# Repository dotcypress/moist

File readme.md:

# moist

🌻 Soil Moisture Sensor

# Resources

* [Schematics](https://kicanvas.org/?github=https://github.com/dotcypress/moist/blob/main/pcb/moist.kicad_sch)
* [PCB](https://kicanvas.org/?github=https%3A%2F%2Fgithub.com%2Fdotcypress%2Fmoist%2Fblob%2Fmain%2Fpcb%2Fmoist.kicad_pcb)
* [BOM](https://htmlpreview.github.io/?https://github.com/dotcypress/moist/blob/main/pcb/bom/ibom.html)

## License

Licensed under either of

- Apache License, Version 2.0 ([LICENSE-APACHE](LICENSE-APACHE) or
  http://www.apache.org/licenses/LICENSE-2.0)
- MIT license ([LICENSE-MIT](LICENSE-MIT) or http://opensource.org/licenses/MIT)

at your option.

### Contribution

Unless you explicitly state otherwise, any contribution intentionally submitted
for inclusion in the work by you, as defined in the Apache-2.0 license, shall be
dual licensed as above, without any additional terms or conditions.

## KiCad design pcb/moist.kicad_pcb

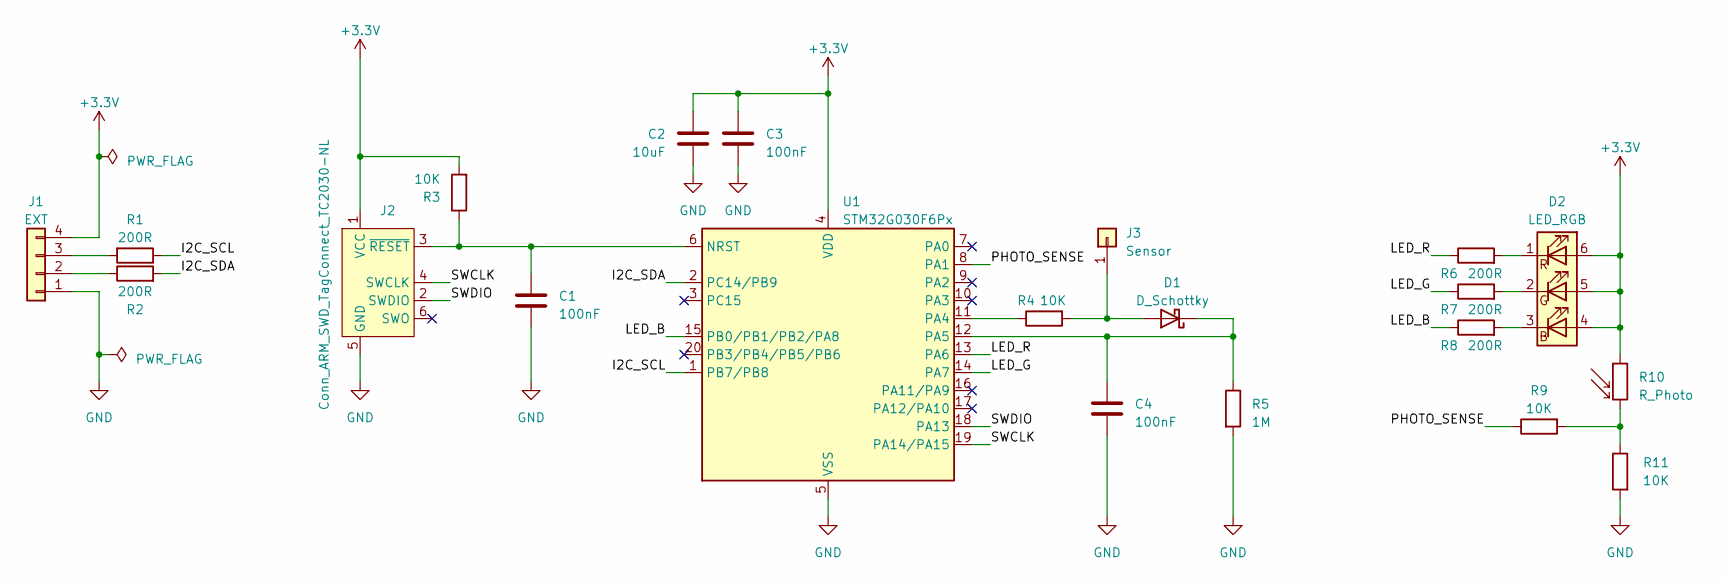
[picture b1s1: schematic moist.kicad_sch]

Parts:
C1, C3, C4: 100nF; C_0603_1608Metric
C2: 10uF; C_0603_1608Metric
D1: D_Schottky; D_0603_1608Metric
D2: LED_RGB; LED_RGB_PLCC-6
J1: EXT; SolderWire-0.1sqmm_1x04_P3.6mm_D0.4mm_OD1mm_Relief
J2: Conn_ARM_SWD_TagConnect_TC2030-NL; Tag-Connect_TC2030-IDC-NL_2x03_P1.27mm_Vertical
J3: Sensor; SensorPad
R1, R2, R6, R7, R8: 200R; R_0603_1608Metric
R3, R4, R9, R11: 10K; R_0603_1608Metric
R5: 1M; R_0603_1608Metric
R10: R_Photo; R_Axial_DIN0204_L3.6mm_D1.6mm_P1.90mm_Vertical
U1: STM32G030F6Px; TSSOP-20_4.4x6.5mm_P0.65mm

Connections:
+3.3V: C2.1, C3.1, D2.4 (BA), D2.5 (GA), D2.6 (RA), J1.4, J2.1 (VCC), R3.2, R10.1, U1.4 (VDD)
/I2C_SCL: R1.1, U1.1 (PB7/PB8)
/I2C_SDA: R2.2, U1.2 (PC14/PB9)
/LED_B: R8.1, U1.15 (PB0/PB1/PB2/PA8)
/LED_G: R7.1, U1.14 (PA7)
/LED_R: R6.1, U1.13 (PA6)
/PHOTO_SENSE: R9.1, U1.8 (PA1)
/SWCLK: J2.4 (SWCLK), U1.19 (PA14/PA15)
/SWDIO: J2.2 (SWDIO), U1.18 (PA13)
GND: C1.2, C2.2, C3.2, C4.2, J1.1, J2.5 (GND), R5.2, R11.2, U1.5 (VSS)
unnamed: D1.2 (A), J3.1, R4.2
unnamed: C4.1, D1.1 (K), R5.1, U1.12 (PA5)
unnamed: D2.3 (BK), R8.2
unnamed: D2.2 (GK), R7.2
unnamed: D2.1 (RK), R6.2
unnamed: J1.2, R2.1
unnamed: J1.3, R1.2
unnamed: C1.1, J2.3 (~RESET), R3.1, U1.6 (NRST)
unnamed: R9.2, R10.2, R11.1
unnamed: R4.1, U1.11 (PA4)

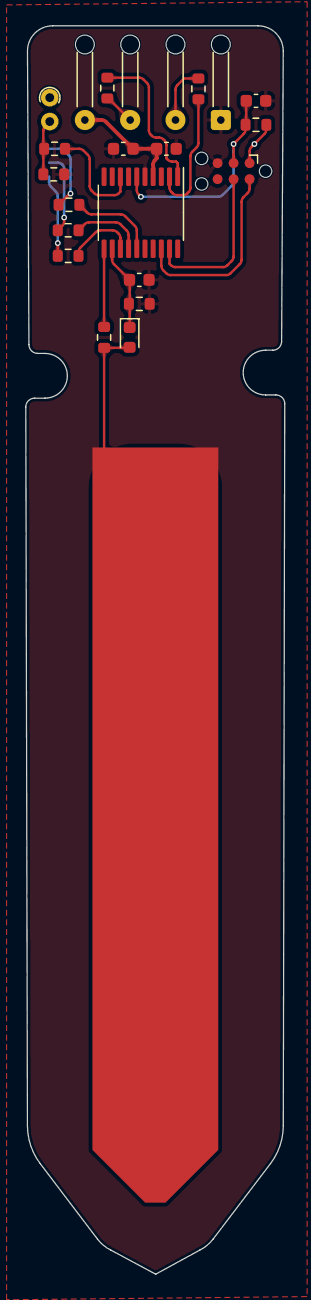
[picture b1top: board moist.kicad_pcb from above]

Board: 2 copper layers, 20.6 x 99.2 mm, 21 parts (1 on the bottom side), 20 nets.

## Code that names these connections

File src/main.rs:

#![no_std]
#![no_main]

extern crate panic_halt;
extern crate rtic;
extern crate stm32g0xx_hal as hal;

mod app;
mod config;
mod server;

use defmt_rtt as _;

use app::*;
use config::*;
use hal::analog::adc;
use hal::flash::{self, WriteErase};
use hal::gpio::*;
use hal::i2c;
use hal::pac::FLASH;
use hal::prelude::*;
use hal::stm32;
use hal::timer::pwm::PwmPin;
use hal::timer::*;

pub const ADDRESS: Address = 0x22;

pub type I2cClk = PB8<Output<OpenDrain>>;
pub type I2cSda = PB9<Output<OpenDrain>>;
pub type I2cDev = i2c::I2c<stm32::I2C1, I2cSda, I2cClk>;
pub type Sense = (adc::Adc, PA5<Analog>, PA1<Analog>);
pub type Led = (
    PwmPin<stm32::TIM3, Channel3>,
    PwmPin<stm32::TIM3, Channel2>,
    PwmPin<stm32::TIM3, Channel1>,
);

#[rtic::app(device = hal::stm32, peripherals = true, dispatchers = [CEC, PVD])]
mod moist {
    use super::*;

    #[shared]
    struct Shared {
        app: App,
    }

    #[local]
    struct Local {
        sense: Sense,
        i2c: I2cDev,
        led: Led,
        timer: Timer<stm32::TIM16>,
        flash: Option<stm32::FLASH>,
    }

    #[init]
    fn init(ctx: init::Context) -> (Shared, Local, init::Monotonics) {
        defmt::info!("init");

        let flash = Some(ctx.device.FLASH);
        let mut rcc = ctx.device.RCC.constrain();

        let port_a = ctx.device.GPIOA.split(&mut rcc);
        let port_b = ctx.device.GPIOB.split(&mut rcc);

        let mut i2c_cfg = i2c::Config::new(400.kHz());
        i2c_cfg.slave_address(ADDRESS);

        let mut i2c = ctx.device.I2C1.i2c(
            port_b.pb9.into_open_drain_output(),
            port_b.pb8.into_open_drain_output(),
            i2c_cfg,
            &mut rcc,
        );
        i2c.listen(i2c::Event::AddressMatch);

        let moisture_sense = port_a.pa5;
        let photo_sense = port_a.pa1;
        let mut adc = ctx.device.ADC.constrain(&mut rcc);
        adc.set_sample_time(adc::SampleTime::T_160);
        adc.set_precision(adc::Precision::B_12);
        adc.set_oversampling_ratio(adc::OversamplingRatio::X_16);
        adc.set_oversampling_shift(16);
        adc.oversampling_enable(true);

        let pwm = ctx.device.TIM14.pwm(200.kHz(), &mut rcc);
        let mut pwm = pwm.bind_pin(port_a.pa4);
        pwm.set_duty(pwm.get_max_duty() / 8);
        pwm.enable();

        let cfg = Config::load();
        let app = App::new(cfg);

        let mut timer = ctx.device.TIM16.timer(&mut rcc);
        timer.start(100.millis());
        timer.listen();

        let led_pwm = ctx.device.TIM3.pwm(1.kHz(), &mut rcc);
        let mut pwm_r = led_pwm.bind_pin(port_b.pb0);
        let mut pwm_g = led_pwm.bind_pin(port_a.pa7);
        let mut pwm_b = led_pwm.bind_pin(port_a.pa6);
        let duty = pwm_r.get_max_duty() + 1;
        pwm_r.set_duty(duty);
        pwm_g.set_duty(duty);
        pwm_b.set_duty(duty);
        pwm_r.enable();
        pwm_g.enable();
        pwm_b.enable();

        let led = (pwm_r, pwm_g, pwm_b);

        defmt::info!("init completed");
        (
            Shared { app },
            Local {
                i2c,
                timer,
                led,
                flash,
                sense: (adc, moisture_sense, photo_sense),
            },
            init::Monotonics(),
        )
    }

    #[task(binds = TIM16, local = [timer, sense], shared = [app])]
    fn timer_tick(ctx: timer_tick::Context) {
        let timer_tick::LocalResources { timer, sense } = ctx.local;
        let mut app = ctx.shared.app;
        let moisture = u16::MAX - sense.0.read(&mut sense.1).unwrap_or(0);
        let illuminance = sense.0.read(&mut sense.2).unwrap_or(0);
        app.lock(|app| app.push_samples(moisture, illuminance));

        timer.clear_irq();
    }

    #[task(priority = 2, binds = I2C1, local = [i2c], shared=[app])]
    fn i2c_rx(ctx: i2c_rx::Context) {
        let mut app = ctx.shared.app;
        match app.lock(|app| app.poll(ctx.local.i2c)) {
            Ok(Some(AppRequest::SetLedColor(color))) => {
                update_led::spawn(color).ok();
            }
            Ok(Some(AppRequest::SaveConfig(cfg))) => {
                save_nvm::spawn(cfg).ok();
            }
            Err(err) => {
                match err {
                    i2c::Error::Overrun => defmt::error!("Overrun"),
                    i2c::Error::Nack => defmt::error!("Nack"),
                    i2c::Error::PECError => defmt::error!("PEC Fault"),
                    i2c::Error::BusError => defmt::error!("Bus Fault"),
                    i2c::Error::ArbitrationLost => defmt::error!("Arbitration lost"),
                    i2c::Error::IncorrectFrameSize(s) => {
                        defmt::error!("Incorrect frame size: {}", s)
                    }
                };
            }
            _ => (),
        }
    }

    #[task(priority = 2, local = [led])]
    fn update_led(ctx: update_led::Context, color: [u8; 3]) {
        let max = ctx.local.led.0.get_max_duty() as u32 + 1;
        ctx.local.led.0.set_duty(max - color[0] as u32 * 256);
        ctx.local.led.1.set_duty(max - color[1] as u32 * 256);
        ctx.local.led.2.set_duty(max - color[2] as u32 * 256);
    }

    #[task(priority = 3, local = [flash])]
    fn save_nvm(ctx: save_nvm::Context, cfg: Config) {
        if let Some(flash) = ctx.local.flash.take() {
            *ctx.local.flash = Some(cfg.save(flash));
        }
    }

    #[idle]
    fn idle(_: idle::Context) -> ! {
        loop {
            rtic::export::nop();
        }
    }
}

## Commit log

2023-05-07 rev 0x01
2023-06-21 led registers
